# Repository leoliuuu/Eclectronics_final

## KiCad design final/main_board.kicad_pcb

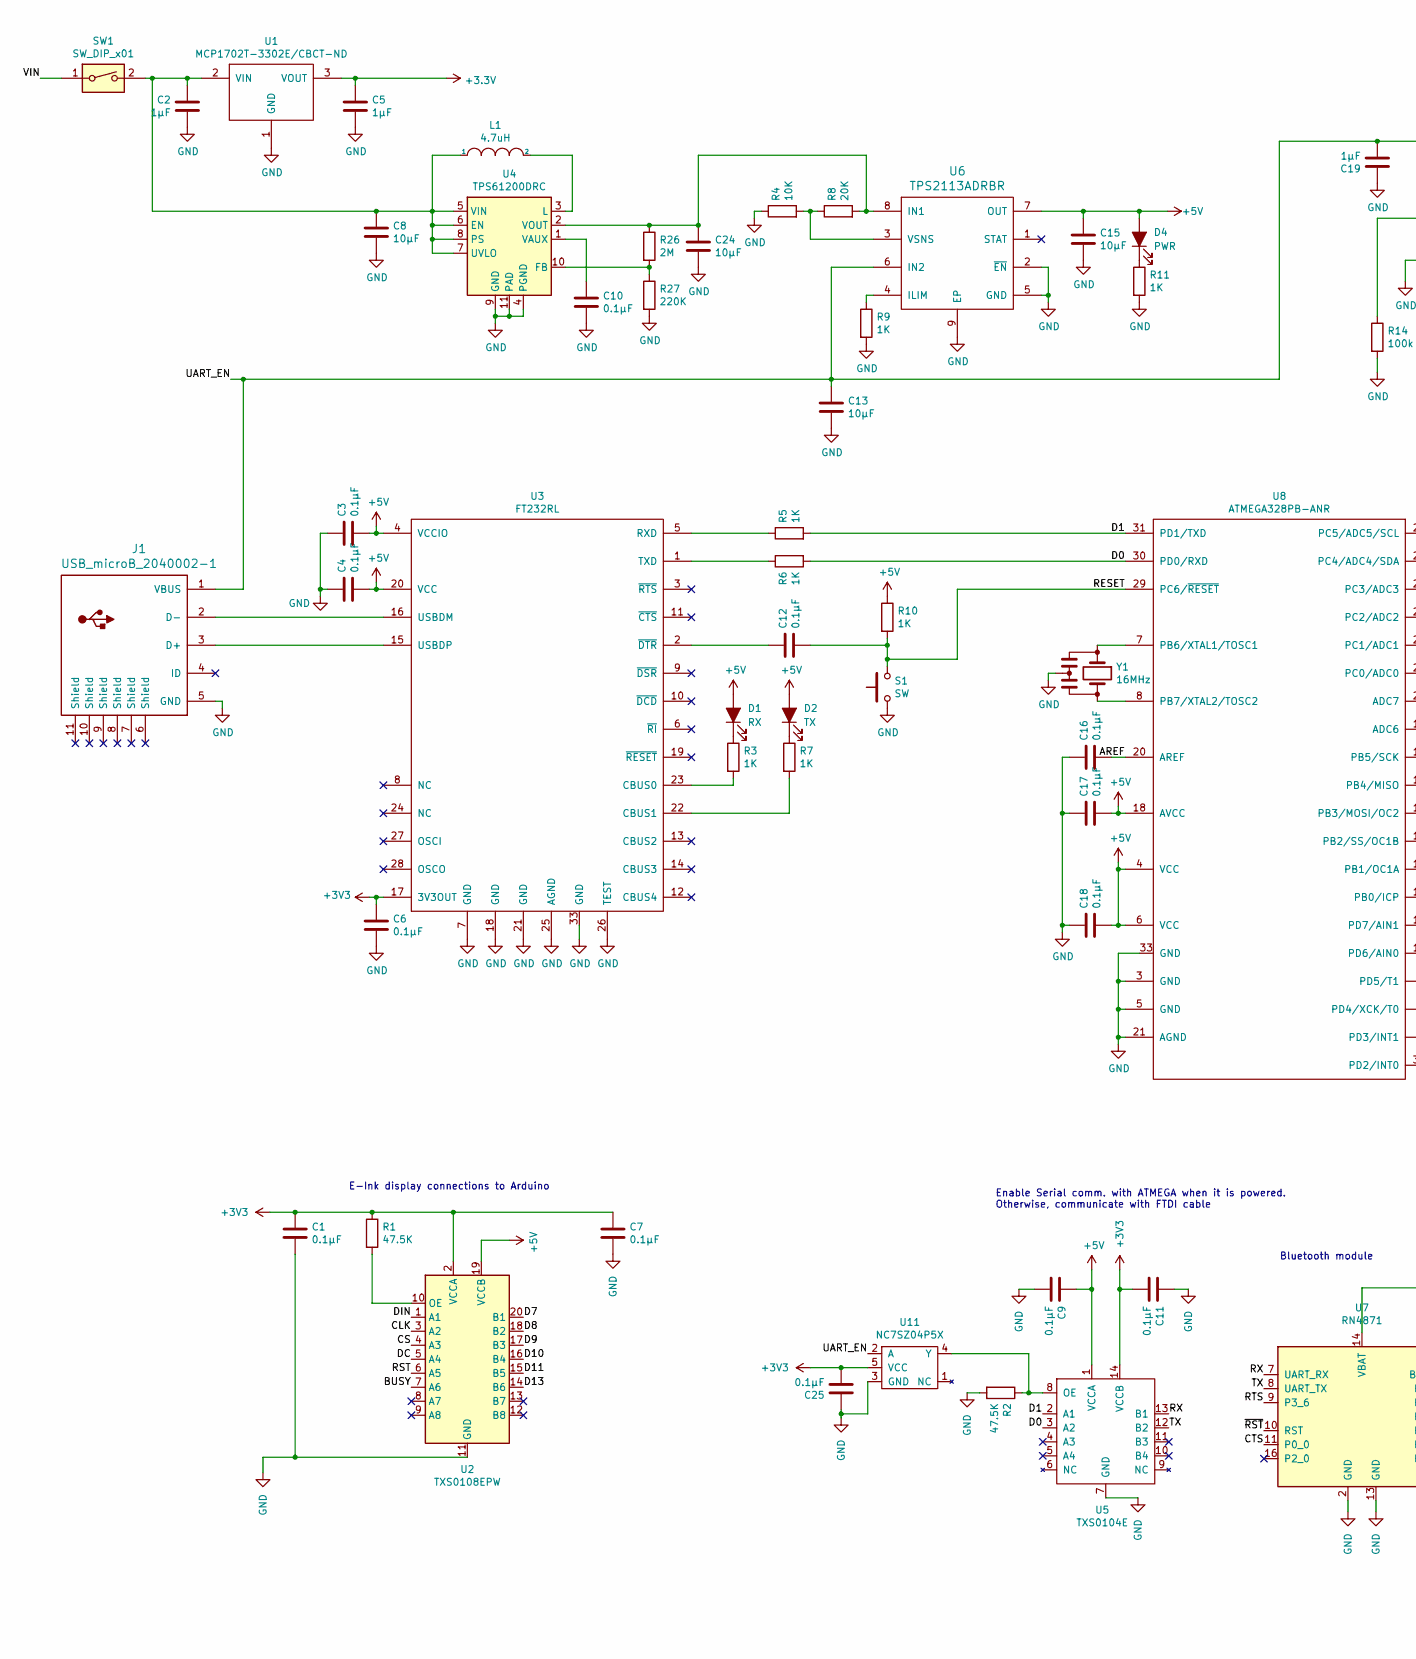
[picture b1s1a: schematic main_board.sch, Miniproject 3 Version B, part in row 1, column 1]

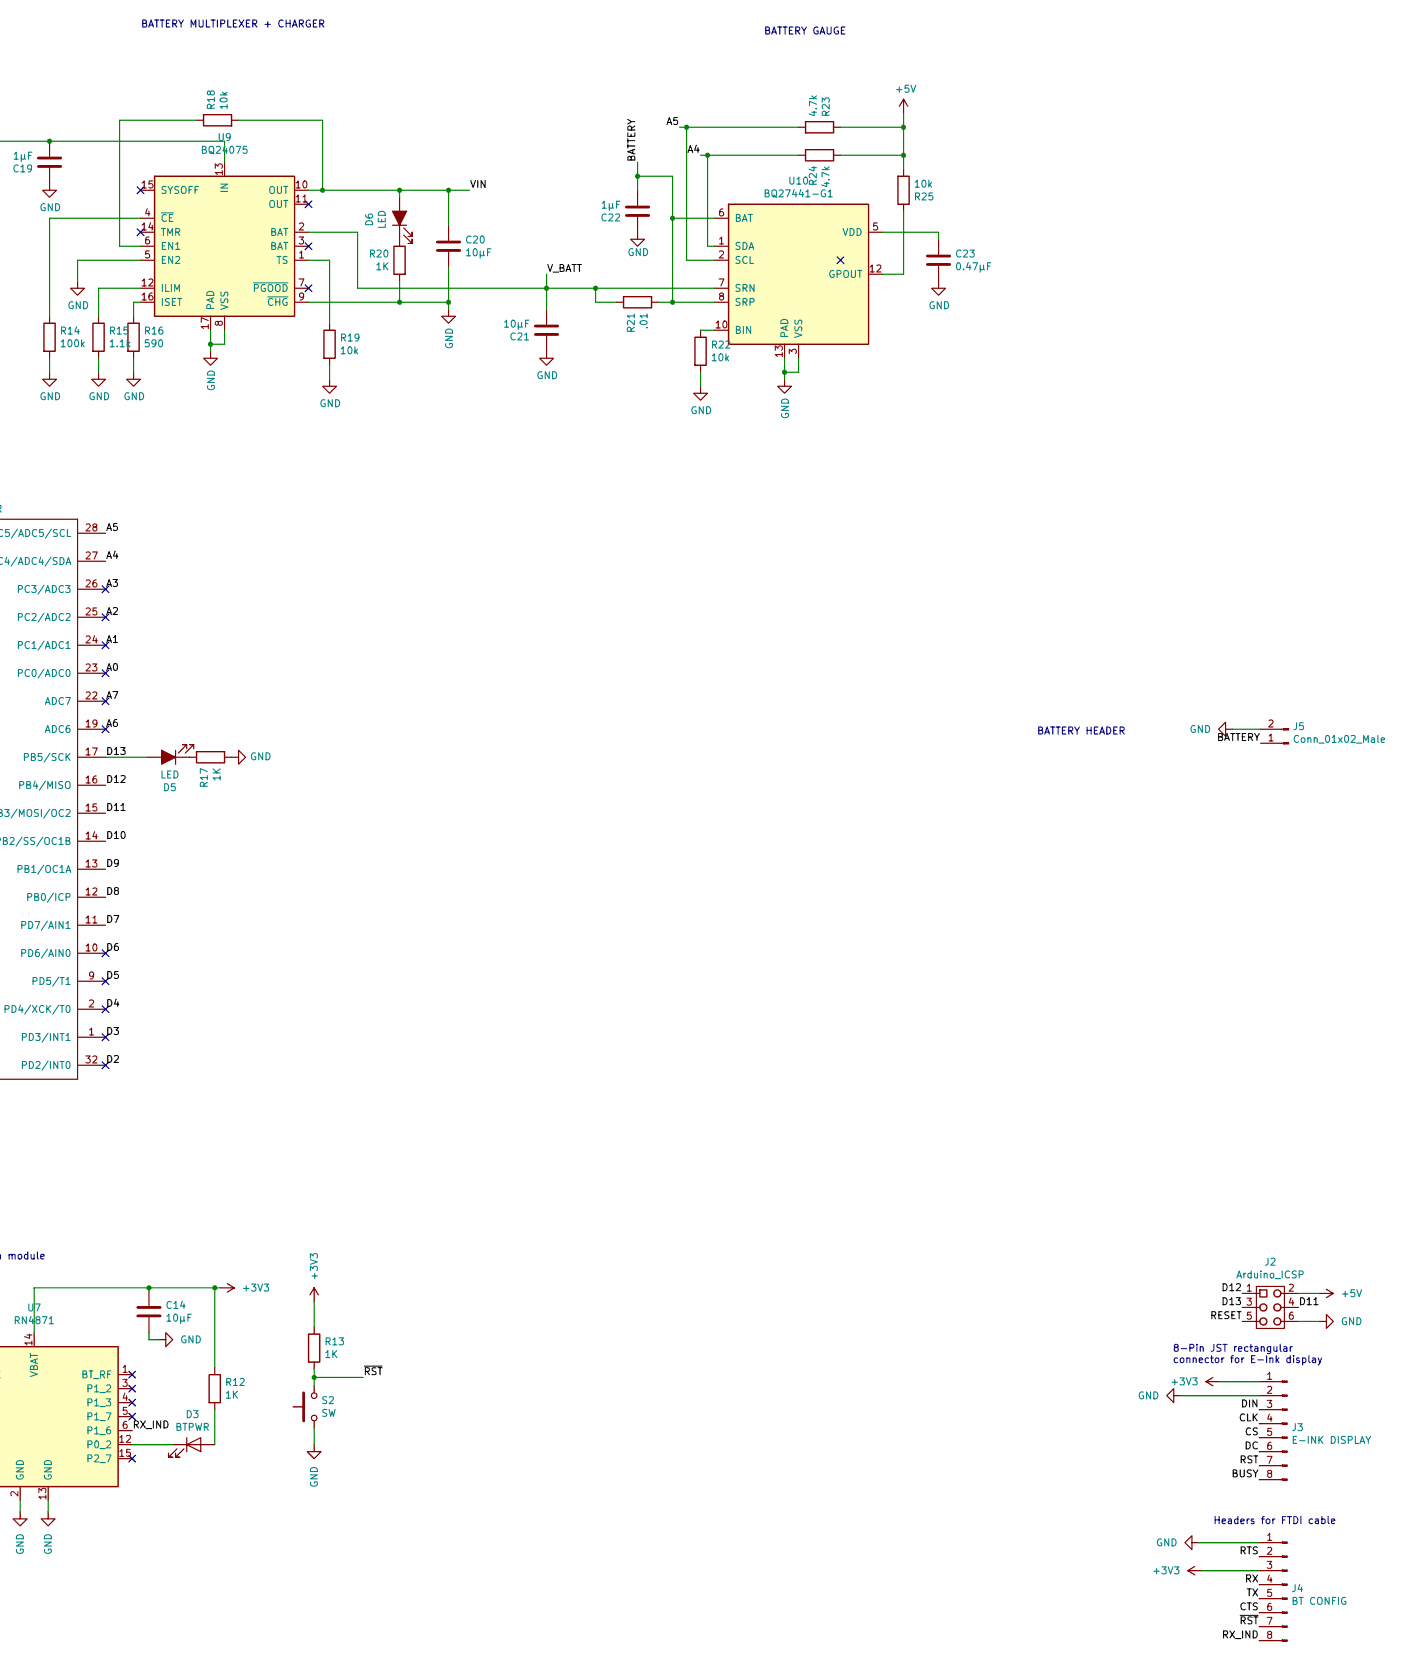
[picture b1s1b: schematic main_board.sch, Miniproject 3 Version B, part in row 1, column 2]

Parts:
C1, C3, C4, C6, C7, C9, C10, C11, C12, C16, C17, C18, C25: 0.1µF; C_0603_1608Metric
C2, C5, C19, C22: 1µF; C_0603_1608Metric
C8, C20, C21, C24: 10µF; C_0603_1608Metric
C13, C14, C15: 10µF; C_0805_2012Metric
C23: 0.47µF; C_0402_1005Metric
D1: RX; LED_0805_2012Metric
D2: TX; LED_0805_2012Metric
D3: BTPWR; LED_0805_2012Metric
D4: PWR; LED_0805_2012Metric
D5, D6: LED; LED_0805_2012Metric
J1: USB_microB_2040002-1
J2: Arduino_ICSP
J3: E-INK DISPLAY; JST_PH_B8B-PH-SM4-TB_1x08-1MP_P2.00mm_Vertical
J4: BT CONFIG; PinHeader_1x08_P2.54mm_Vertical
J5: Conn_01x02_Male; JST-2-SMD
L1: 4.7uH; CDRH2D18HP
R1, R2: 47.5K; R_0603_1608Metric
R3, R5, R6, R7, R9, R10, R11, R12, R13, R17, R20: 1K; R_0603_1608Metric
R4: 10K; R_0603_1608Metric
R8: 20K; R_0603_1608Metric
R14: 100k; R_0603_1608Metric
R15: 1.1k; R_0603_1608Metric
R16: 590; R_0603_1608Metric
R18, R19, R22, R25: 10k; R_0603_1608Metric
R21: .01; R_0603_1608Metric
R23, R24: 4.7k; R_0603_1608Metric
R26: 2M; R_0603_1608Metric
R27: 220K; R_0603_1608Metric
S1, S2: SW; SW_SPST_B3U-1000P
SW1: SW_DIP_x01; KAE01SGGt
U1: MCP1702T-3302E/CBCT-ND; SOT-23
U2: TXS0108EPW; TSSOP-20_4.4x6.5mm_P0.65mm
U3: FT232RL; FT232RQ
U4: TPS61200DRC
U5: TXS0104E; txs0104e
U6: TPS2113ADRBR
U7: RN4871; Microchip_RN4871
U8: ATMEGA328PB-ANR; Atmega328pb
U9: BQ24075
U10: BQ27441-G1; Texas_S-PDSO-N12
U11: NC7SZ04P5X
Y1: 16MHz; CSTNE

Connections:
+5V: C3.2, C4.2, C9.1, C15.1, C17.2, C18.2, D1.2 (A), D2.2 (A), D4.2 (A), J2.2, R10.1, R23.1, R24.2, R25.2, U2.19 (VCCB), U3.4 (VCCIO), U3.20 (VCC), U5.1 (VCCA), U6.7 (OUT), U8.4 (VCC), U8.6 (VCC), U8.18 (AVCC)
/A0: U8.23 (PC0/ADC0)
/A1: U8.24 (PC1/ADC1)
/A2: U8.25 (PC2/ADC2)
/A3: U8.26 (PC3/ADC3)
/A4: R24.1, U8.27 (PC4/ADC4/SDA), U10.1 (SDA)
/A5: R23.2, U8.28 (PC5/ADC5/SCL), U10.2 (SCL)
/A6: U8.19 (ADC6)
/A7: U8.22 (ADC7)
/AREF: C16.2, U8.20 (AREF)
/BATTERY: C22.2, J5.1, R21.2, U10.6 (BAT), U10.8 (SRP)
/BUSY: J3.8, U2.7 (A6)
/CLK: J3.4, U2.3 (A2)
/CS: J3.5, U2.4 (A3)
/CTS: J4.6, U7.11 (P0_0)
/D0: R6.2, U5.3 (A2), U8.30 (PD0/RXD)
/D1: R5.2, U5.2 (A1), U8.31 (PD1/TXD)
/D2: U8.32 (PD2/INT0)
/D3: U8.1 (PD3/INT1)
/D4: U8.2 (PD4/XCK/T0)
/D5: U8.9 (PD5/T1)
/D6: U8.10 (PD6/AIN0)
/D7: U2.20 (B1), U8.11 (PD7/AIN1)
/D8: U2.18 (B2), U8.12 (PB0/ICP)
/D9: U2.17 (B3), U8.13 (PB1/OC1A)
/D10: U2.16 (B4), U8.14 (PB2/SS/OC1B)
/D11: J2.4, U2.15 (B5), U8.15 (PB3/MOSI/OC2)
/D12: J2.1, U8.16 (PB4/MISO)
/D13: D5.2 (A), J2.3, U2.14 (B6), U8.17 (PB5/SCK)
/DC: J3.6, U2.5 (A4)
/DIN: J3.3, U2.1 (A1)
/RESET: C12.2, J2.5, R10.2, S1.2, U8.29 (PC6/~RESET)
/RST: J3.7, U2.6 (A5)
/RTS: J4.2, U7.9 (P3_6)
/RX: J4.4, U5.13 (B1), U7.7 (UART_RX)
/RX_IND: J4.8, U7.6 (P1_6)
/TX: J4.5, U5.12 (B2), U7.8 (UART_TX)
/UART_EN: C13.1, C19.2, J1.1 (VBUS), U6.6 (IN2), U9.13 (IN), U11.2 (A)
/VIN: C20.1, D6.2 (A), R18.2, SW1.1, U9.10 (OUT)
/V_BATT: C21.2, R21.1, U9.2 (BAT), U10.7 (SRN)
/~RST: J4.7, R13.2, S2.2, U7.10 (RST)
GND: C1.2, C2.2, C3.1, C4.1, C5.2, C6.2, C7.2, C8.2, C9.2, C10.2, C11.1, C13.2, C14.2, C15.2, C16.1, C17.1, C18.1, C19.1, C20.2, C21.1, C22.1, C23.2, C24.2, C25.1, J1.5 (GND), J2.6, J3.2, J4.1, J5.2, R2.2, R4.1, R9.2, R11.2, R14.2, R15.2, R16.2, R17.2, R19.2, R20.2, R22.2, R27.2, S1.1, S2.1, U1.1 (GND), U2.11 (GND), U3.7 (GND), U3.18 (GND), U3.21 (GND), U3.25 (AGND), U3.26 (TEST), U3.33 (GND), U4.4 (PGND), U4.9 (GND), U4.11 (PAD), U5.7 (GND), U6.2 (~EN), U6.5 (GND), U6.9 (EP), U7.2 (GND), U7.13 (GND), U8.3 (GND), U8.5 (GND), U8.21 (AGND), U8.33 (GND), U9.5 (EN2), U9.8 (VSS), U9.9 (~CHG), U9.17 (PAD), U10.3 (VSS), U10.13 (PAD), U11.3 (GND), Y1.2
unnamed: C2.1, C8.1, L1.1, SW1.2, U1.2 (VIN), U4.5 (VIN), U4.6 (EN), U4.7 (UVLO), U4.8 (PS)
unnamed: C10.1, U4.1 (VAUX)
unnamed: C12.1, U3.2 (~DTR)
unnamed: C23.1, U10.5 (VDD)
unnamed: C24.1, R8.2, R26.1, U4.2 (VOUT), U6.8 (IN1)
unnamed: D1.1 (K), R3.1
unnamed: D2.1 (K), R7.1
unnamed: D3.1 (K), U7.12 (P0_2)
unnamed: D3.2 (A), R12.2
unnamed: D4.1 (K), R11.1
unnamed: D5.1 (K), R17.1
unnamed: D6.1 (K), R20.1
unnamed: J1.2 (D-), U3.16 (USBDM)
unnamed: J1.3 (D+), U3.15 (USBDP)
unnamed: L1.2, U4.3 (L)
unnamed: R1.2, U2.10 (OE)
unnamed: R2.1, U5.8 (OE), U11.4 (Y)
unnamed: R3.2, U3.23 (CBUS0)
unnamed: R4.2, R8.1, U6.3 (VSNS)
unnamed: R5.1, U3.5 (RXD)
unnamed: R6.1, U3.1 (TXD)
unnamed: R7.2, U3.22 (CBUS1)
unnamed: R9.1, U6.4 (ILIM)
unnamed: R14.1, U9.4 (~CE)
unnamed: R15.1, U9.12 (ILIM)
unnamed: R16.1, U9.16 (ISET)
unnamed: R18.1, U9.6 (EN1)
unnamed: R19.1, U9.1 (TS)
unnamed: R22.1, U10.10 (BIN)
unnamed: R25.1, U10.12 (GPOUT)
unnamed: R26.2, R27.1, U4.10 (FB)
unnamed: U8.7 (PB6/XTAL1/TOSC1), Y1.1
unnamed: U8.8 (PB7/XTAL2/TOSC2), Y1.3

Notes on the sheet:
8-Pin JST rectangular connector for E-Ink display
Headers for FTDI cable
E-Ink display connections to Arduino
Enable Serial comm. with ATMEGA when it is powered. Otherwise, communicate with FTDI cable
Bluetooth module
BATTERY MULTIPLEXER + CHARGER
BATTERY GAUGE
BATTERY HEADER

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
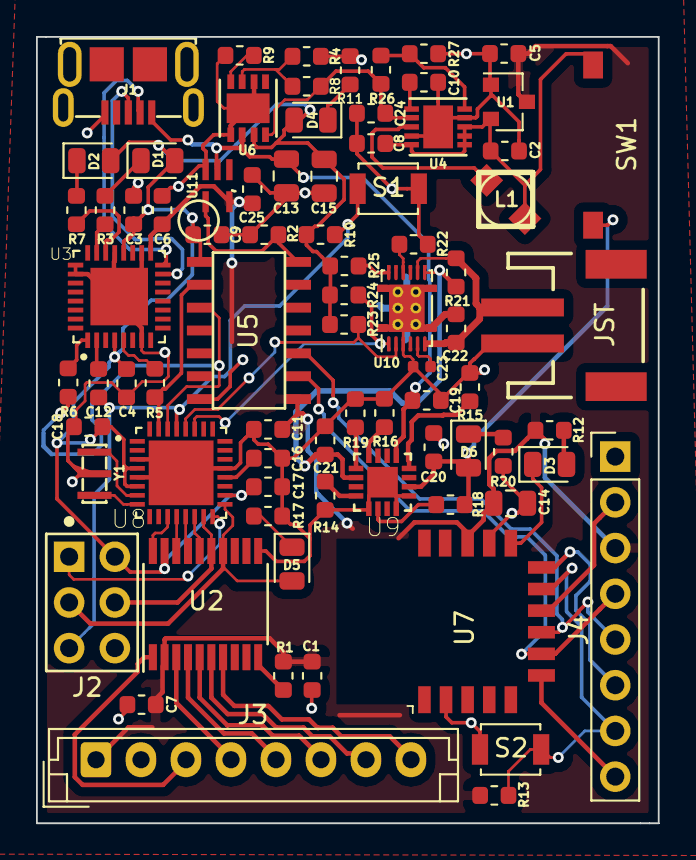
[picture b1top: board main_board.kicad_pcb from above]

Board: 2 copper layers, 34.5 x 43.7 mm, 79 parts (0 on the bottom side), 65 nets.

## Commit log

2019-04-02 Initialize project for display subsystem
2019-04-02 Populate with first pass schematic
2019-04-02 Add files for custom project symbol library
2019-04-07 Finish schematics
2019-04-08 Power Added
2019-04-08 Revert "Power Added"
    This reverts commit 6e914afe56b2ec69bab62107e6ad54a93b9b43d6.
2019-04-08 Add mode button
2019-04-08 Fix merge conflicts
2019-04-08 Add mode button.
2019-04-08 Clean up
2019-04-08 Add diode to 3V3 output of FTDI and power display from Lin Reg.
2019-04-09 Hook up reset on BT to MCU
2019-04-11 Added Power Schematic
2019-04-11 Update Power 4/11
2019-04-11 Ground pins
2019-04-11 Made Boards Better
2019-04-14 Update Main Board
2019-04-16 Create inverter symbol
2019-04-16 Add inverter and change enable
2019-04-16 Linear Regulator -> Boost DC-DC
2019-04-16 Footprint assignment
2019-04-16 Footprint Assigned
2019-04-16 Change pull up/down resistor values for logic level enable pins
2019-04-16 Made footprints
2019-04-16 Assign new footprint to capacitor
2019-04-16 Add Footprint for Inductor
2019-04-16 made footprint
2019-04-16 footprint
2019-04-16 Footprints
2019-04-17 added new footprints and assignments
2019-04-17 Assigned footprints
2019-04-18 Footprint additions
2019-04-18 Assign footprints
2019-04-18 Create footprints
2019-04-18 Bluetooth Power LED Footprint Assigned
2019-04-18 Add assignment for small logic converter
2019-04-18 Final Footprints
2019-04-18 Fixed bad junction
2019-04-18 Fixed Something
2019-04-18 Footprint Update + layout main
2019-04-18 Change jst footprint assignment
2019-04-18 Modified main Layout
2019-04-20 Layout
2019-04-22 board layout position complete
2019-04-22 sensor board layout updates
2019-04-22 Add ground pad to QFNs
2019-04-22 Updated Layout
2019-04-22 Update 1
2019-04-22 Update 2
2019-04-23 Final_Push
2019-04-23 sensor board layout progress
2019-04-23 Update 3
2019-04-24 changes to senor layout
2019-04-25 Add code to convert and image to a usable format
2019-04-25 Make test script for displaying images and text
2019-04-25 Add library that compiles correctly
2019-04-25 sensor board layout complete
2019-04-25 sensor board final fix and is now ready for fab
2019-04-25 Fixed Silk
2019-04-25 text added
2019-04-29 Add script for main board
2019-05-01 Add speed calculations
2019-05-02 Add code for the sensor board
2019-05-02 Debugging
2019-05-06 Load new images
2019-05-06 Add display code
2019-05-06 Add background images
2019-05-07 Add functions for fuel guage and battery display
